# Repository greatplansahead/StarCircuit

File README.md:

# StarCircuit

Basically an analog flip-flop circuit that you can use only when it is dark! It is also keychainable and has encouraging bible verses on it!

# Schematic

# PCB

#BOM
- 1xbattery holder
- 2xLEDs
- 2x4.7k resistors
- 2x220 resistors
- 1x47k resistors
- 3xNPN transistors
- 1xPhotoresistors
- 2xPushbuttons

Made by @Nunu on slack
Part of hack Club's Solder YSWS

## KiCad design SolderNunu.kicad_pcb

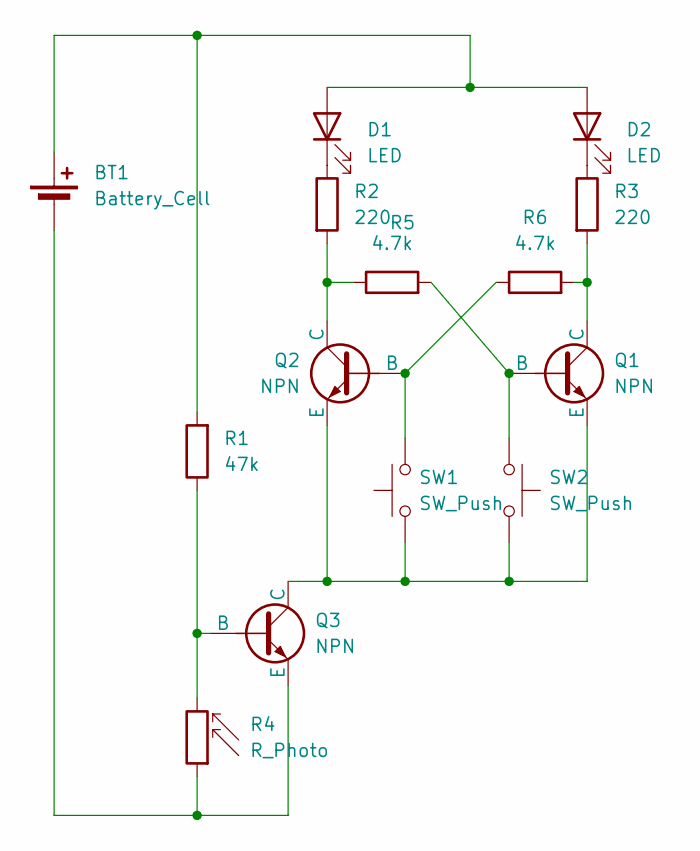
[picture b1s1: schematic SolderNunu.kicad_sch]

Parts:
BT1: Battery_Cell; BatteryHolder_Keystone_3034_1x20mm
D1, D2: LED; LED_D5.0mm
Q1, Q2, Q3: NPN; TO-92L_HandSolder
R1: 47k; R_Axial_DIN0207_L6.3mm_D2.5mm_P7.62mm_Horizontal
R2, R3: 220; R_Axial_DIN0207_L6.3mm_D2.5mm_P7.62mm_Horizontal
R4: R_Photo; R_LDR_5.1x4.3mm_P3.4mm_Vertical
R5, R6: 4.7k; R_Axial_DIN0207_L6.3mm_D2.5mm_P7.62mm_Horizontal
SW1, SW2: SW_Push; SW_PUSH_6mm

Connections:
unnamed: BT1.1 (+), D1.2 (A), D2.2 (A), R1.2
unnamed: BT1.2 (-), Q3.3 (E), R4.1
unnamed: D1.1 (K), R2.1
unnamed: D2.1 (K), R3.1
unnamed: Q1.2 (B), R5.2, SW2.1
unnamed: Q1.1 (C), R3.2, R6.2
unnamed: Q1.3 (E), Q2.3 (E), Q3.1 (C), SW1.1, SW2.2
unnamed: Q2.2 (B), R6.1, SW1.2
unnamed: Q2.1 (C), R2.2, R5.1
unnamed: Q3.2 (B), R1.1, R4.2

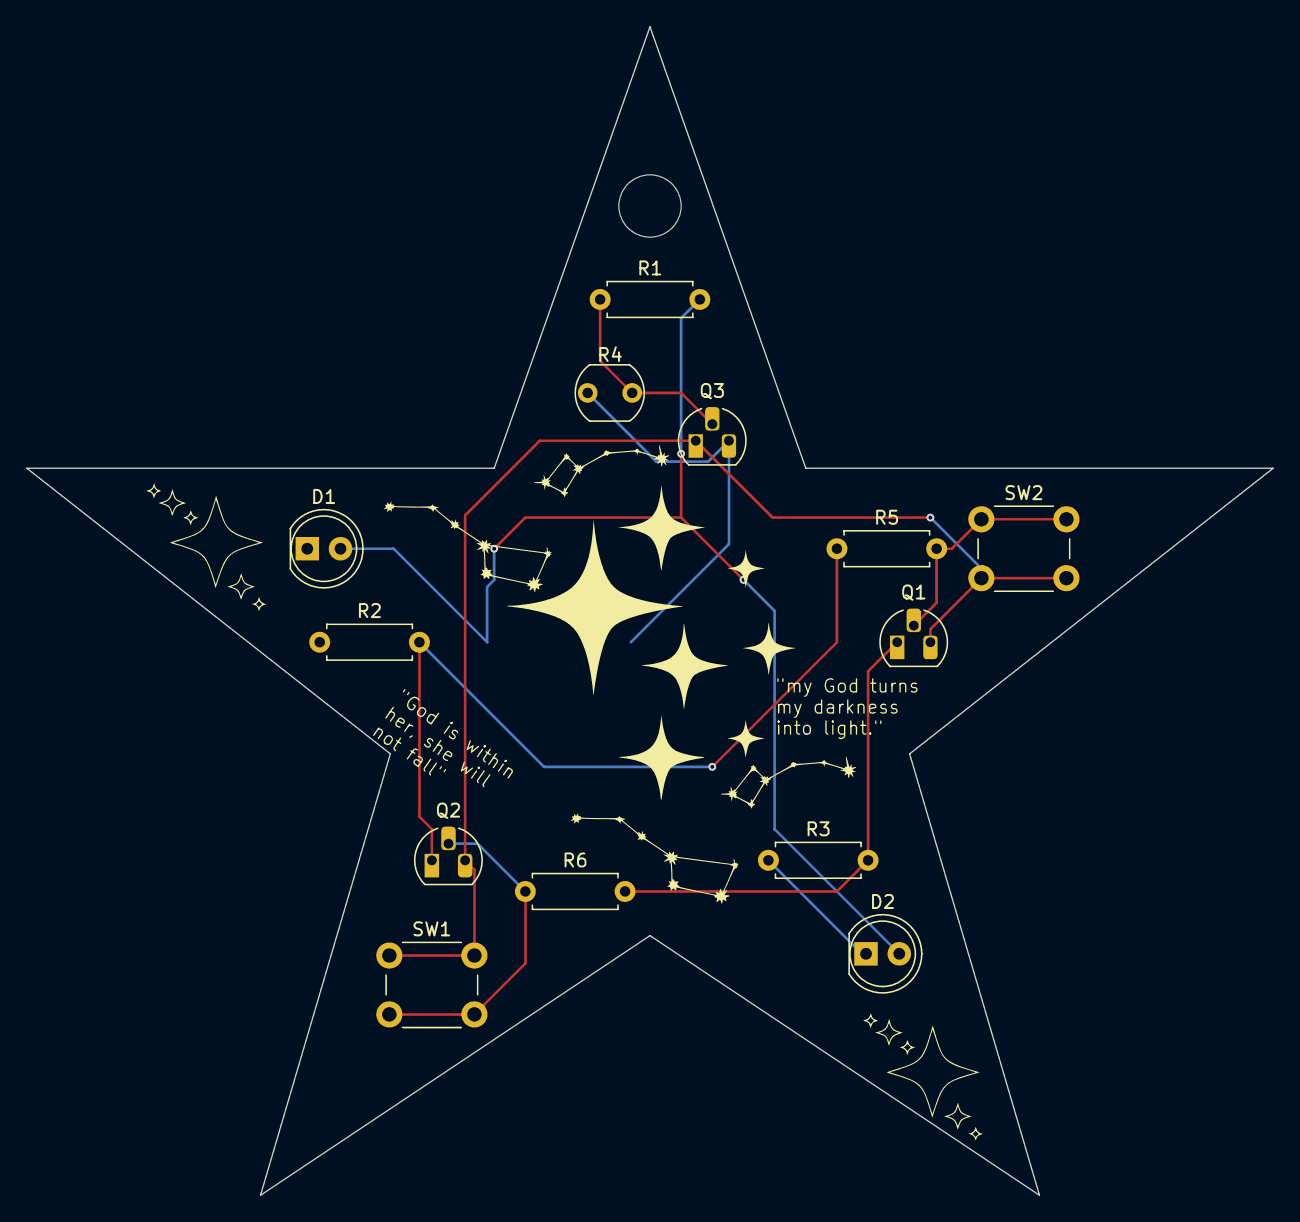
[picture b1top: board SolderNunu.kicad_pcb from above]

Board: 2 copper layers, 95.2 x 89.3 mm, 16 parts (1 on the bottom side), 10 nets.

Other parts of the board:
G: LOGO
G#2: LOGO
